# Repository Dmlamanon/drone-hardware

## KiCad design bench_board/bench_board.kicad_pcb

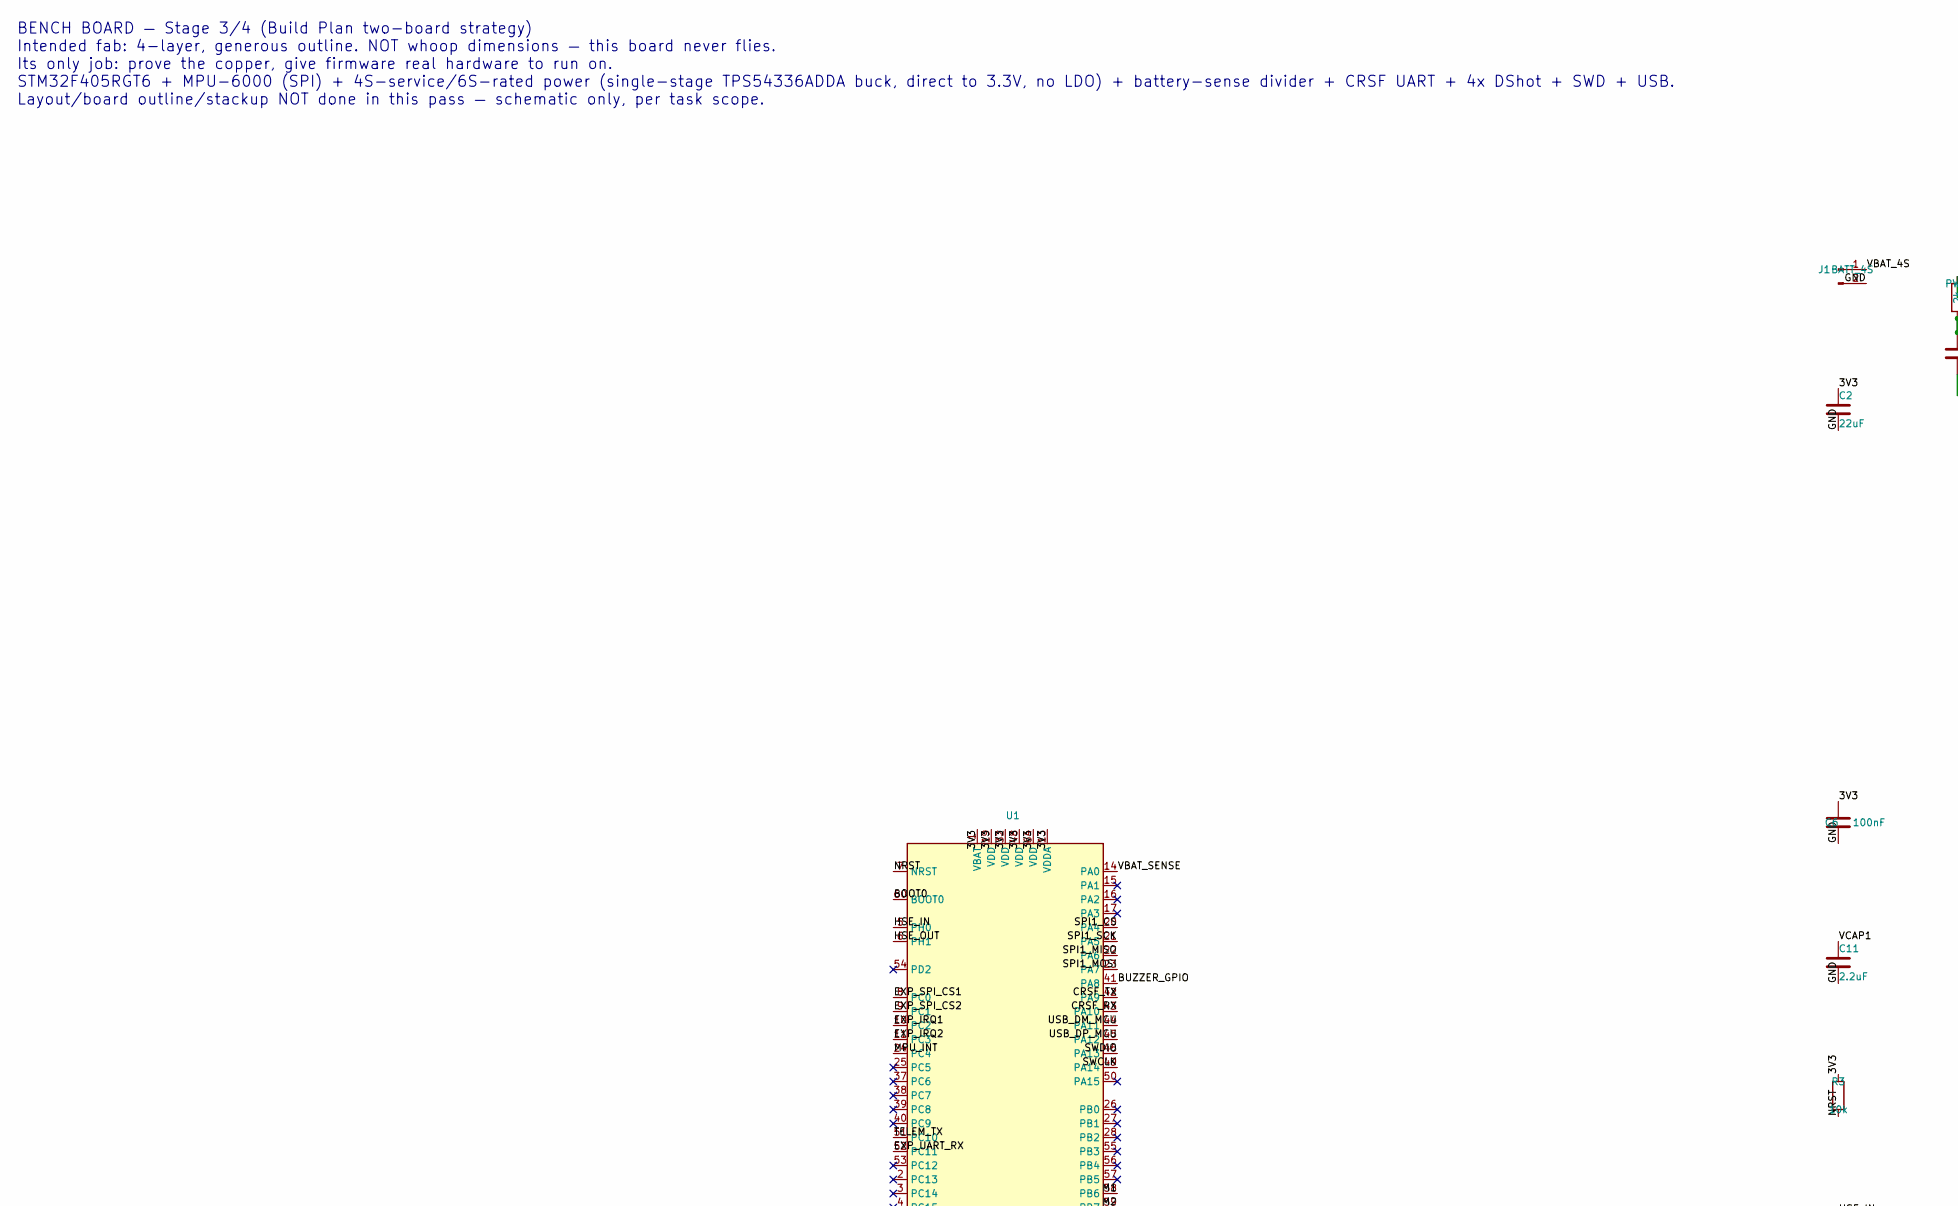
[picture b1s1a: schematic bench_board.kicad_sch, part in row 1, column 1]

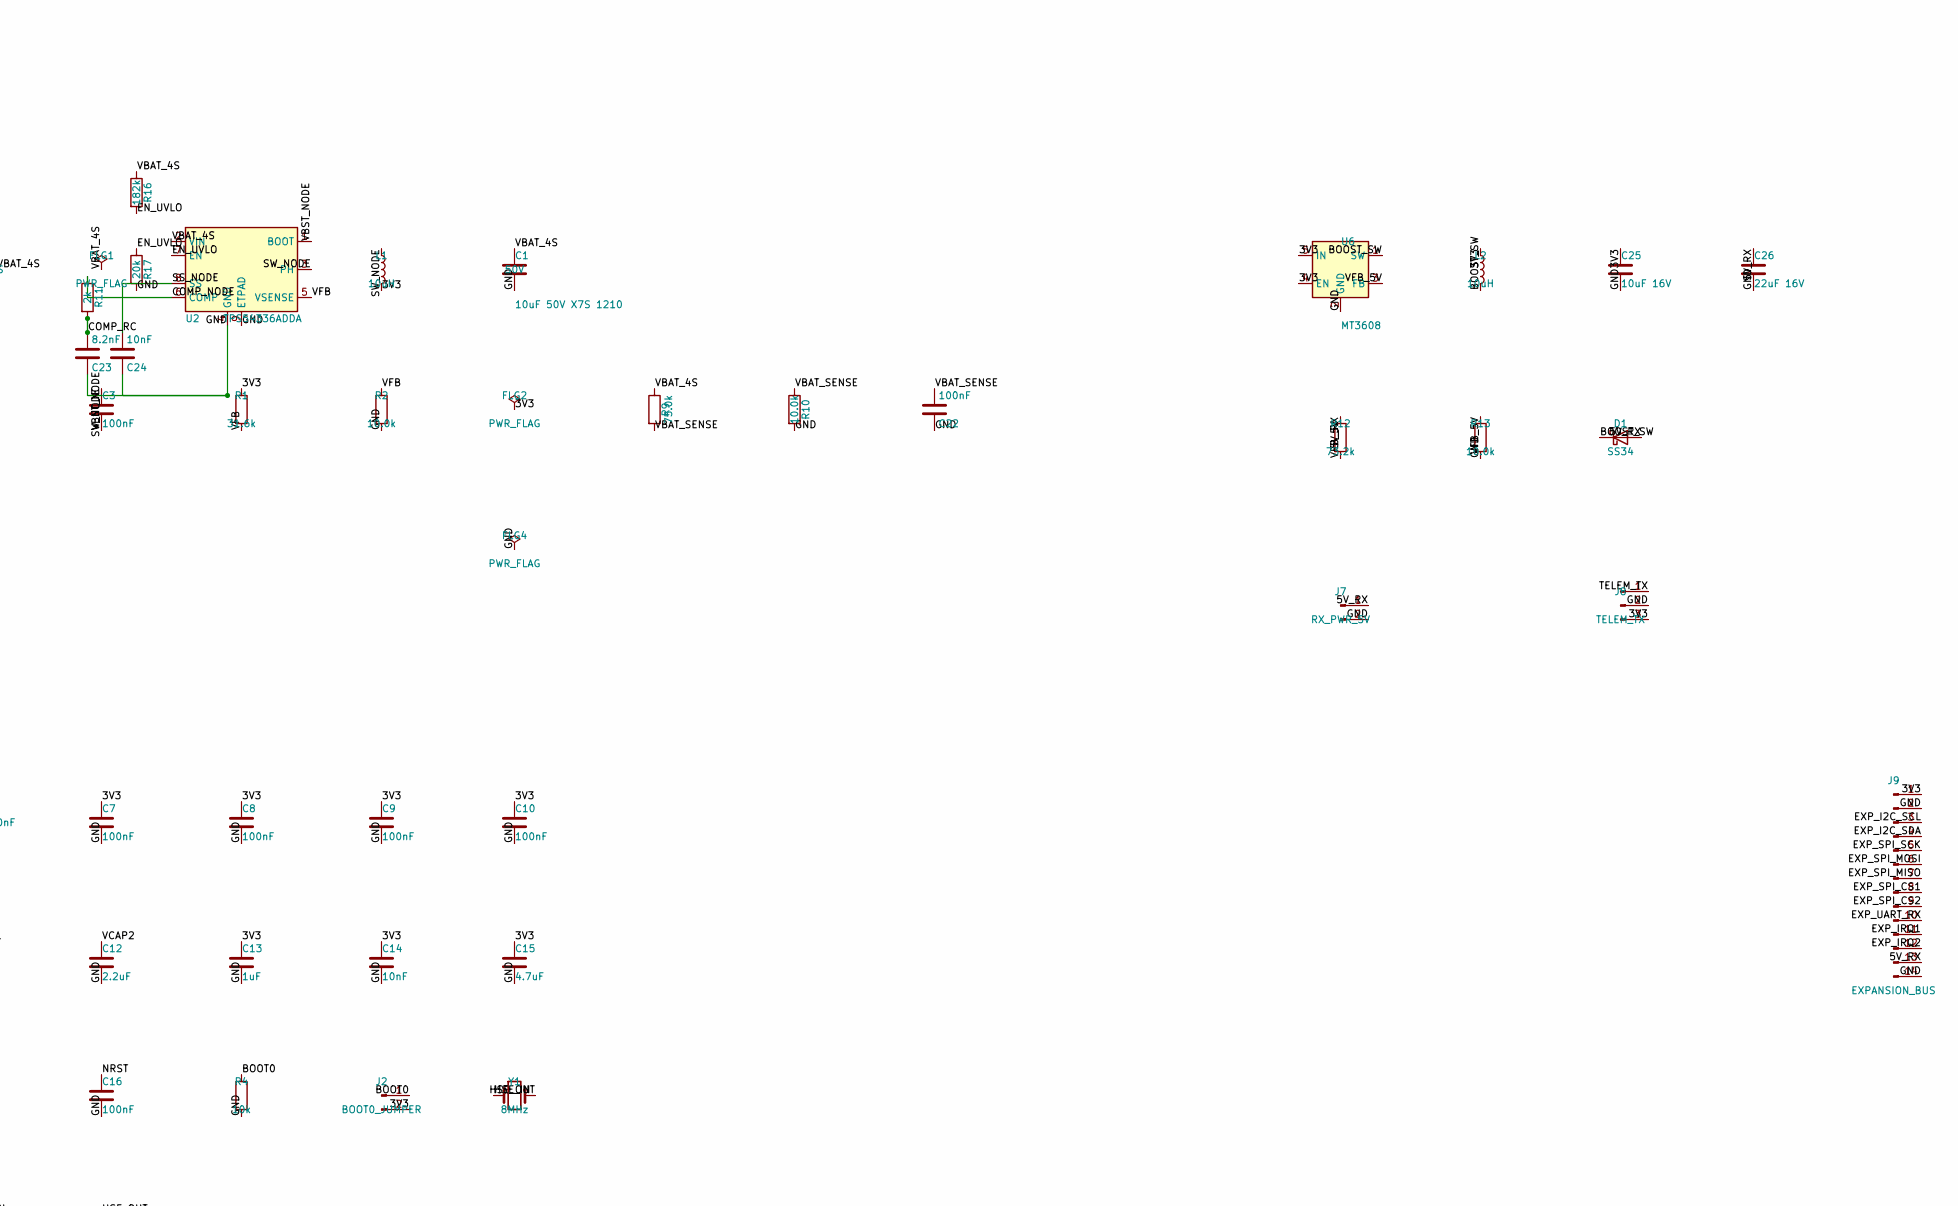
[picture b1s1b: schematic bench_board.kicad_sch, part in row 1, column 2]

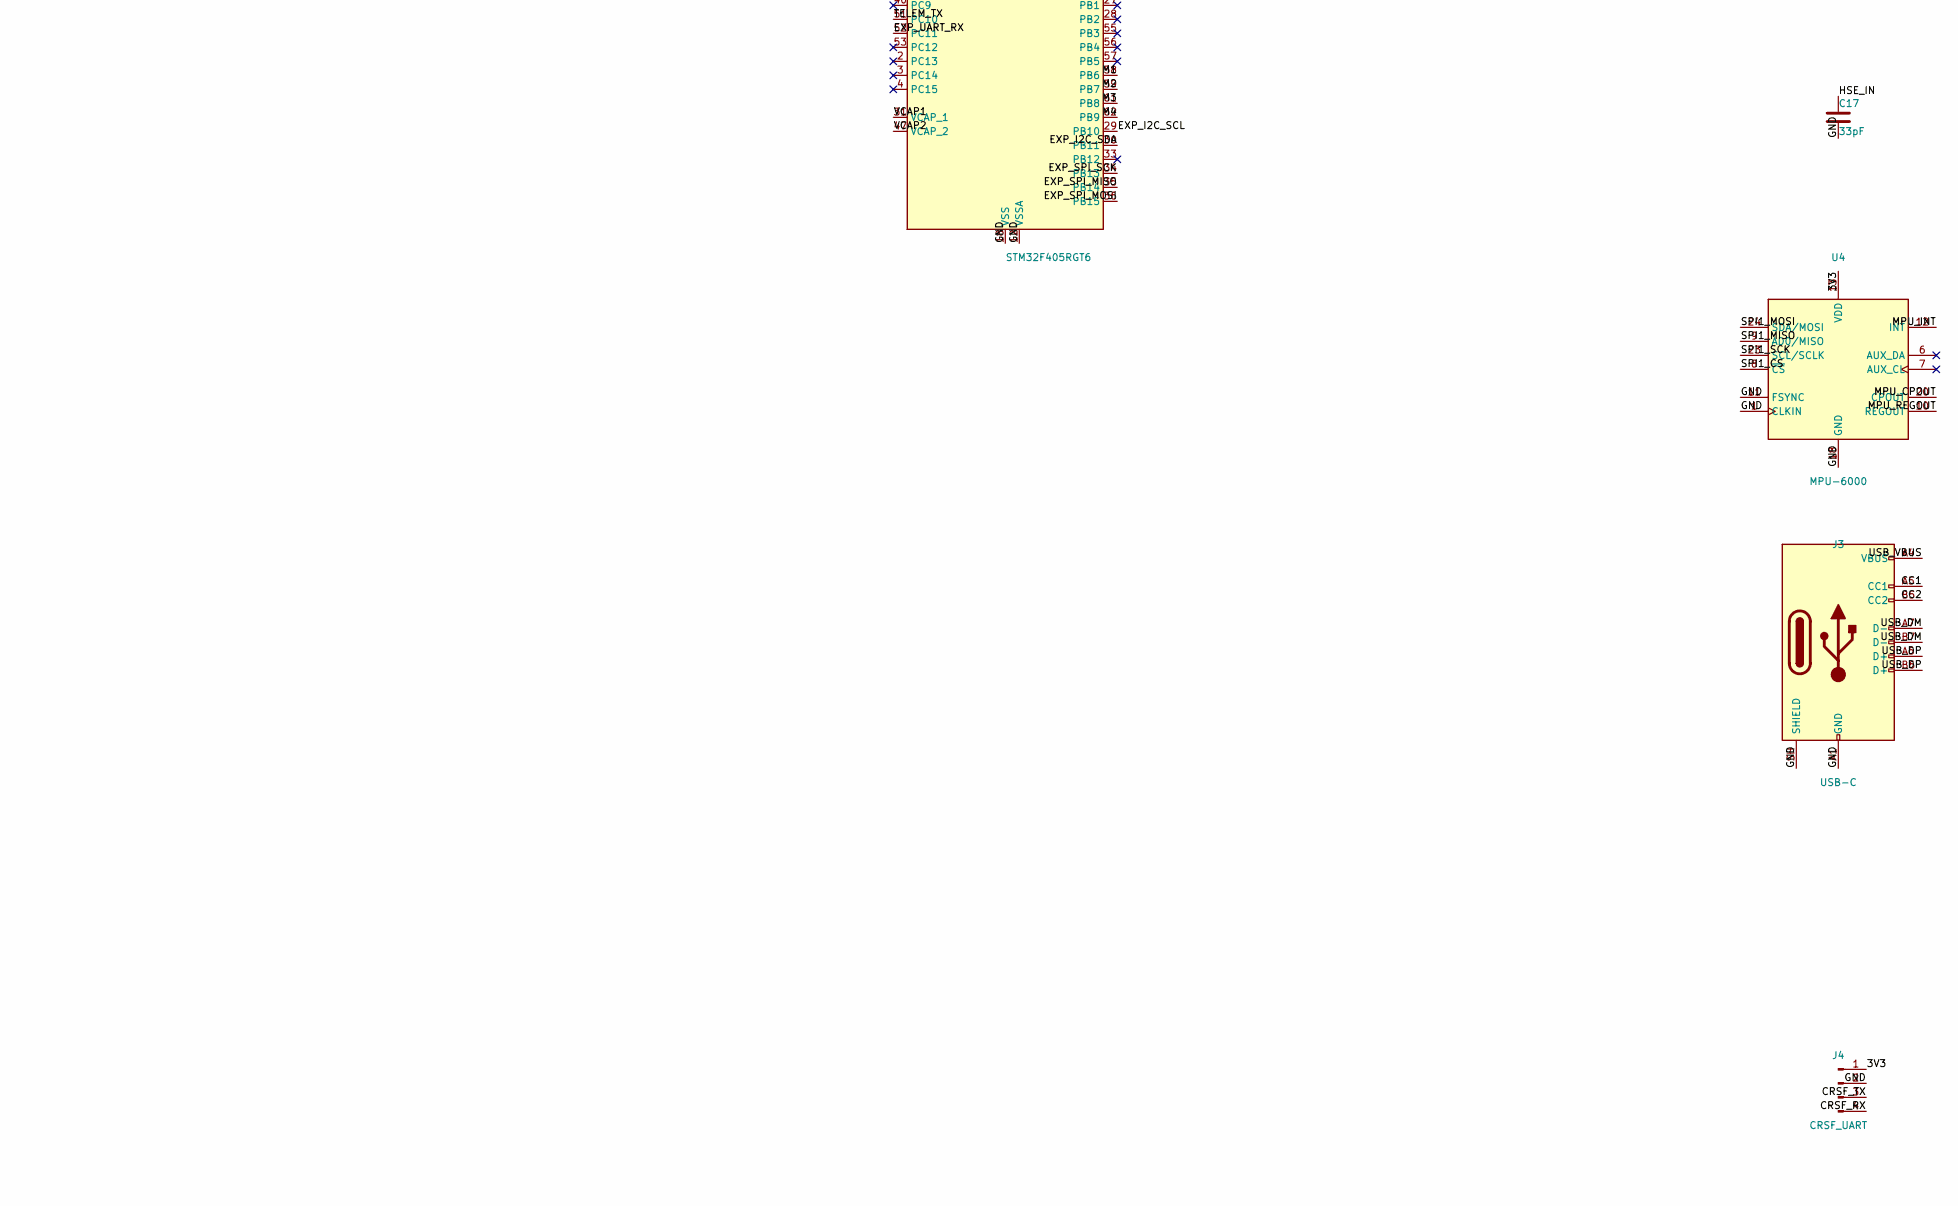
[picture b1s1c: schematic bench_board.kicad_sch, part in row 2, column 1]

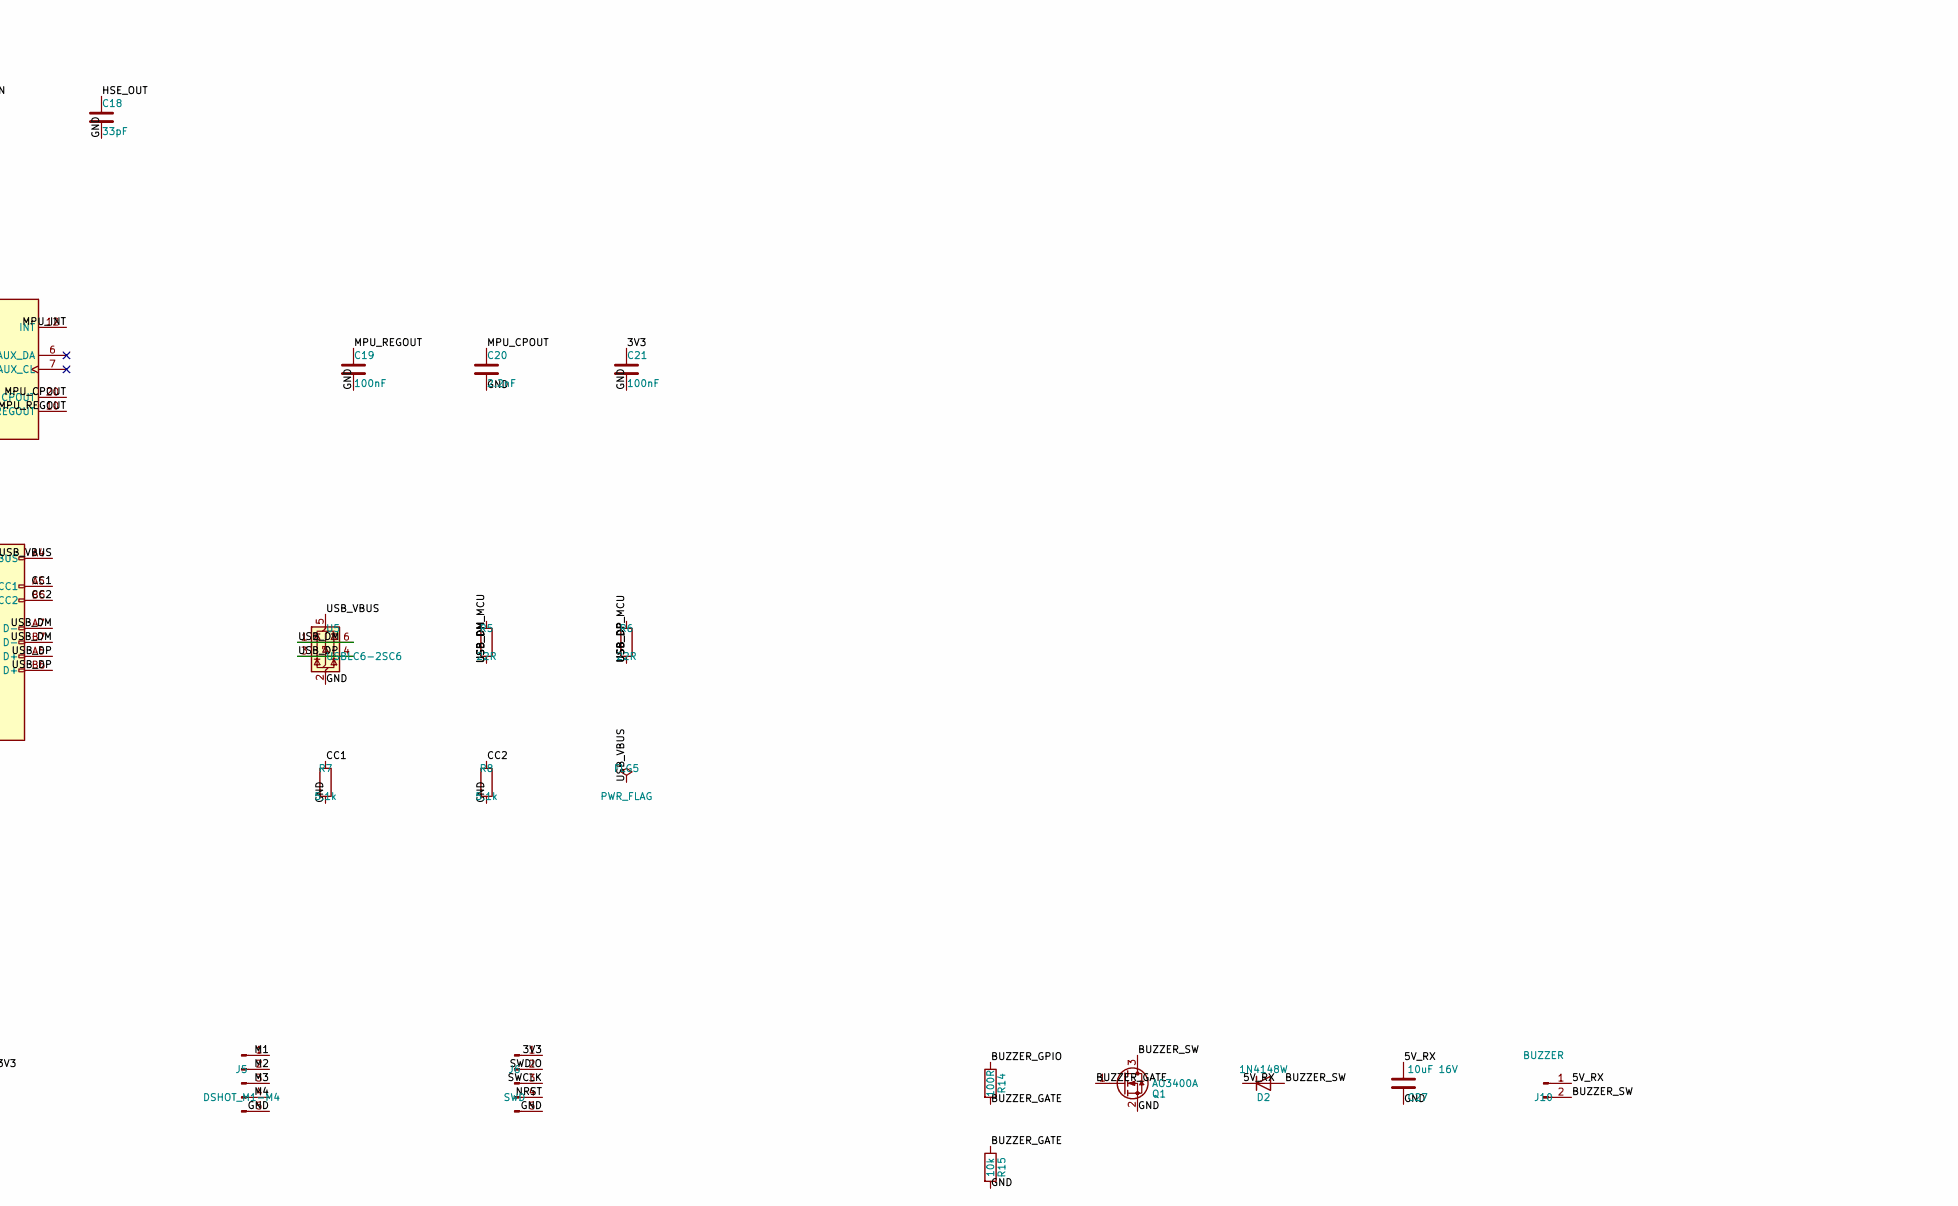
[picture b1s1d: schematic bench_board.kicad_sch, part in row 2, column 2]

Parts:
C1: 10uF 50V X7S 1210; C_1210_3225Metric; Voltage 50V; MPN GRM32ER71H106KA12L
C2: 22uF; C_0805_2012Metric
C3, C6, C7, C8, C9, C10, C16, C19, C21, C22: 100nF; C_0402_1005Metric
C11, C12: 2.2uF; C_0603_1608Metric
C13: 1uF; C_0603_1608Metric
C14, C24: 10nF; C_0402_1005Metric
C15: 4.7uF; C_0805_2012Metric
C17, C18: 33pF; C_0402_1005Metric; Voltage 50V; LCSC C1562
C20: 2.2nF; C_0402_1005Metric; Voltage 50V; LCSC C106861
C23: 8.2nF; C_0402_1005Metric
C25, C27: 10uF 16V; C_0805_2012Metric
C26: 22uF 16V; C_0805_2012Metric
D1: SS34; D_SMA
D2: 1N4148W; D_SOD-123
FLG1, FLG2, FLG4, FLG5: PWR_FLAG
J1: BATT_4S; PinHeader_1x02_P2.54mm_Vertical
J2: BOOT0_JUMPER; PinHeader_1x02_P2.54mm_Vertical
J3: USB-C; USB_C_Receptacle_Amphenol_12401548E4-2A
J4: CRSF_UART; PinHeader_1x04_P2.54mm_Vertical
J5: DSHOT_M1-M4; PinHeader_1x05_P2.54mm_Vertical
J6: SWD; PinHeader_1x05_P2.54mm_Vertical
J7: RX_PWR_5V; PinHeader_1x02_P2.54mm_Vertical
J8: TELEM_TX; PinHeader_1x03_P2.54mm_Vertical
J9: EXPANSION_BUS; PinHeader_1x14_P2.54mm_Vertical
J10: BUZZER; PinHeader_1x02_P2.54mm_Vertical
L1, L2: 10uH; L_1210_3225Metric
Q1: AO3400A; SOT-23
R1: 31.6k; R_0402_1005Metric
R2, R10: 10.0k; R_0402_1005Metric
R3, R4, R15: 10k; R_0402_1005Metric
R5, R6: 22R; R_0402_1005Metric
R7, R8: 5.1k; R_0402_1005Metric
R9: 75.0k; R_0402_1005Metric
R11: 2k; R_0402_1005Metric
R12: 73.2k; R_0603_1608Metric
R13: 10.0k; R_0603_1608Metric
R14: 100R; R_0402_1005Metric
R16: 182k; R_0402_1005Metric; Tolerance 1%; LCSC C11481
R17: 20k; R_0402_1005Metric; Tolerance 1%; LCSC C25765
U1: STM32F405RGT6; LQFP-64_10x10mm_P0.5mm
U2: TPS54336ADDA; SOIC-8-1EP_3.9x4.9mm_P1.27mm_EP2.41x3.81mm
U4: MPU-6000; InvenSense_QFN-24_4x4mm_P0.5mm
U5: USBLC6-2SC6; SOT-23-6
U6: MT3608; SOT-23-6
Y1: 8MHz; Crystal_SMD_5032-2Pin_5.0x3.2mm; LCSC C115962

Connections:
/3V3: C2.1, C6.1, C7.1, C8.1, C9.1, C10.1, C13.1, C14.1, C15.1, C21.1, C25.1, FLG2.1, J2.2, J4.1, J6.1, J8.3, J9.1, L1.2, L2.1, R1.1, R3.1, U1.1 (VBAT), U1.13 (VDDA), U1.19 (VDD), U1.32 (VDD), U1.48 (VDD), U1.64 (VDD), U4.13 (VDD), U6.4 (EN), U6.5 (IN)
/5V_RX: C26.1, C27.1, D1.2 (A), D2.1 (K), J7.1, J9.13, J10.1, R12.1
/BOOST_SW: D1.1 (K), L2.2, U6.1 (SW)
/BOOT0: J2.1, R4.1, U1.60 (BOOT0)
/BUZZER_GATE: Q1.1 (G), R14.2, R15.1
/BUZZER_GPIO: R14.1, U1.41 (PA8)
/BUZZER_SW: D2.2 (A), J10.2, Q1.3 (D)
/CC1: J3.A5 (CC1), R7.1
/CC2: J3.B5 (CC2), R8.1
/COMP_NODE: R11.1, U2.6 (COMP)
/COMP_RC: C23.1, R11.2
/CRSF_RX: J4.4, U1.43 (PA10)
/CRSF_TX: J4.3, U1.42 (PA9)
/EN_UVLO: R16.2, R17.1, U2.7 (EN)
/EXP_I2C_SCL: J9.3, U1.29 (PB10)
/EXP_I2C_SDA: J9.4, U1.30 (PB11)
/EXP_IRQ1: J9.11, U1.10 (PC2)
/EXP_IRQ2: J9.12, U1.11 (PC3)
/EXP_SPI_CS1: J9.8, U1.8 (PC0)
/EXP_SPI_CS2: J9.9, U1.9 (PC1)
/EXP_SPI_MISO: J9.7, U1.35 (PB14)
/EXP_SPI_MOSI: J9.6, U1.36 (PB15)
/EXP_SPI_SCK: J9.5, U1.34 (PB13)
/EXP_UART_RX: J9.10, U1.52 (PC11)
/GND: C1.2, C2.2, C6.2, C7.2, C8.2, C9.2, C10.2, C11.2, C12.2, C13.2, C14.2, C15.2, C16.2, C17.2, C18.2, C19.2, C20.2, C21.2, C22.2, C23.2, C24.2, C25.2, C26.2, C27.2, FLG4.1, J1.2, J3.A1 (GND), J3.A12 (GND), J3.B1 (GND), J3.B12 (GND), J3.SH (SHIELD), J4.2, J5.5, J6.5, J7.2, J8.2, J9.2, J9.14, Q1.2 (S), R2.2, R4.2, R7.2, R8.2, R10.2, R13.2, R15.2, R17.2, U1.12 (VSSA), U1.18 (VSS), U1.63 (VSS), U2.4 (GND), U2.9 (ETPAD), U4.1 (CLKIN), U4.11 (FSYNC), U4.18 (GND), U5.2 (GND), U6.2 (GND)
/HSE_IN: C17.1, U1.5 (PH0), Y1.1
/HSE_OUT: C18.1, U1.6 (PH1), Y1.2
/M1: J5.1, U1.58 (PB6)
/M2: J5.2, U1.59 (PB7)
/M3: J5.3, U1.61 (PB8)
/M4: J5.4, U1.62 (PB9)
/MPU_CPOUT: C20.1, U4.20 (CPOUT)
/MPU_INT: U1.24 (PC4), U4.12 (INT)
/MPU_REGOUT: C19.1, U4.10 (REGOUT)
/NRST: C16.1, J6.4, R3.2, U1.7 (NRST)
/SPI1_CS: U1.20 (PA4), U4.8 (~CS)
/SPI1_MISO: U1.22 (PA6), U4.9 (AD0/MISO)
/SPI1_MOSI: U1.23 (PA7), U4.24 (SDA/MOSI)
/SPI1_SCK: U1.21 (PA5), U4.23 (SCL/SCLK)
/SS_NODE: C24.1, U2.8 (SS)
/SWCLK: J6.3, U1.49 (PA14)
/SWDIO: J6.2, U1.46 (PA13)
/SW_NODE: C3.1, L1.1, U2.3 (PH)
/TELEM_TX: J8.1, U1.51 (PC10)
/USB_DM: J3.A7 (D-), J3.B7 (D-), R5.1, U5.1 (I/O1), U5.6 (I/O1)
/USB_DM_MCU: R5.2, U1.44 (PA11)
/USB_DP: J3.A6 (D+), J3.B6 (D+), R6.1, U5.3 (I/O2), U5.4 (I/O2)
/USB_DP_MCU: R6.2, U1.45 (PA12)
/USB_VBUS: FLG5.1, J3.A4 (VBUS), J3.A9 (VBUS), J3.B4 (VBUS), J3.B9 (VBUS), U5.5 (VBUS)
/VBAT_4S: C1.1, FLG1.1, J1.1, R9.1, R16.1, U2.2 (VIN)
/VBAT_SENSE: C22.1, R9.2, R10.1, U1.14 (PA0)
/VBST_NODE: C3.2, U2.1 (BOOT)
/VCAP1: C11.1, U1.31 (VCAP_1)
/VCAP2: C12.1, U1.47 (VCAP_2)
/VFB: R1.2, R2.1, U2.5 (VSENSE)
/VFB_5V: R12.2, R13.1, U6.3 (FB)

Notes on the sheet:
BENCH BOARD — Stage 3/4 (Build Plan two-board strategy) Intended fab: 4-layer, generous outline. NOT whoop dimensions — this board never flies. Its only job: prove the copper, give firmware real hardware to run on. STM32F405RGT6 + MPU-6000 (SPI) + 4S-service/6S-rated power (single-stage TPS54336ADD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

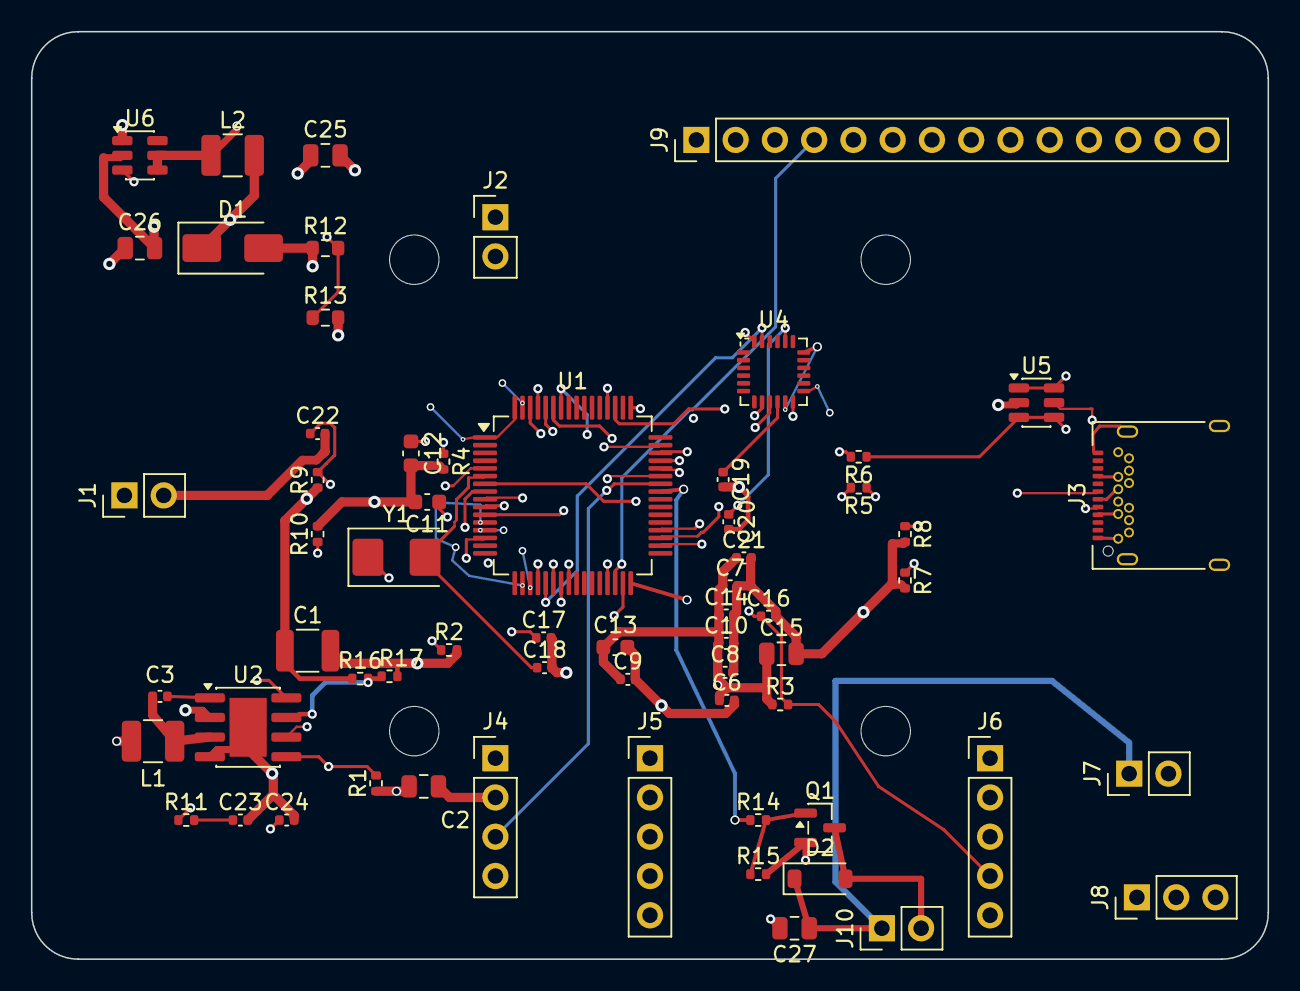
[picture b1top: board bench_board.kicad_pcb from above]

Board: 4 copper layers, 80.0 x 60.0 mm, 67 parts (0 on the bottom side), 56 nets.

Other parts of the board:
MH1, MH2, MH3, MH4: MountingHole_3.2mm; MountingHole_3.2mm_M3

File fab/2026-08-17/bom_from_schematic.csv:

"Reference","Value","Footprint","LCSC","JLCPCB_PN","QUANTITY"
"C1","10uF 50V X7R 1210","Capacitor_SMD:C_1210_3225Metric","","","1"
"C2","22uF","Capacitor_SMD:C_0805_2012Metric","","","1"
"C3,C6-C10,C16,C19-C22","100nF","Capacitor_SMD:C_0402_1005Metric","","","11"
"C11,C12","2.2uF","Capacitor_SMD:C_0603_1608Metric","","","2"
"C13","1uF","Capacitor_SMD:C_0603_1608Metric","","","1"
"C14,C24","10nF","Capacitor_SMD:C_0402_1005Metric","","","2"
"C15","4.7uF","Capacitor_SMD:C_0805_2012Metric","","","1"
"C17,C18","10pF","Capacitor_SMD:C_0402_1005Metric","","","2"
"C23","7.5nF","Capacitor_SMD:C_0402_1005Metric","","","1"
"C25","10uF 16V","Capacitor_SMD:C_0805_2012Metric","","","1"
"C26","22uF 16V","Capacitor_SMD:C_0805_2012Metric","","","1"
"D1","SS34","Diode_SMD:D_SMA","","","1"
"FLG1,FLG2,FLG4,FLG5","PWR_FLAG","","","","4"
"J1","BATT_4S","Connector_PinHeader_2.54mm:PinHeader_1x02_P2.54mm_Vertical","","","1"
"J2","BOOT0_JUMPER","Connector_PinHeader_2.54mm:PinHeader_1x02_P2.54mm_Vertical","","","1"
"J3","USB-C","Connector_USB:USB_C_Receptacle_Amphenol_12401548E4-2A","","","1"
"J4","CRSF_UART","Connector_PinHeader_2.54mm:PinHeader_1x04_P2.54mm_Vertical","","","1"
"J5","DSHOT_M1-M4","Connector_PinHeader_2.54mm:PinHeader_1x05_P2.54mm_Vertical","","","1"
"J6","SWD","Connector_PinHeader_2.54mm:PinHeader_1x05_P2.54mm_Vertical","","","1"
"J7","RX_PWR_5V","Connector_PinHeader_2.54mm:PinHeader_1x02_P2.54mm_Vertical","","","1"
"J8","TELEM_TX","Connector_PinHeader_2.54mm:PinHeader_1x03_P2.54mm_Vertical","","","1"
"J9","EXPANSION_BUS","Connector_PinHeader_2.54mm:PinHeader_1x14_P2.54mm_Vertical","","","1"
"L1,L2","10uH","Inductor_SMD:L_1210_3225Metric","","","2"
"R1","31.6k","Resistor_SMD:R_0402_1005Metric","","","1"
"R2,R10","10.0k","Resistor_SMD:R_0402_1005Metric","","","2"
"R3,R4","10k","Resistor_SMD:R_0402_1005Metric","","","2"
"R5,R6","22R","Resistor_SMD:R_0402_1005Metric","","","2"
"R7,R8","5.1k","Resistor_SMD:R_0402_1005Metric","","","2"
"R9","75.0k","Resistor_SMD:R_0402_1005Metric","","","1"
"R11","2k","Resistor_SMD:R_0402_1005Metric","","","1"
"R12","73.2k","Resistor_SMD:R_0603_1608Metric","","","1"
"R13","10.0k","Resistor_SMD:R_0603_1608Metric","","","1"
"U1","STM32F405RGT6","Package_QFP:LQFP-64_10x10mm_P0.5mm","","","1"
"U2","TPS54336ADDA","Package_SO:SOIC-8-1EP_3.9x4.9mm_P1.27mm_EP2.41x3.81mm","","","1"
"U4","MPU-6000","Sensor_Motion:InvenSense_QFN-24_4x4mm_P0.5mm","","","1"
"U5","USBLC6-2SC6","Package_TO_SOT_SMD:SOT-23-6","","","1"
"U6","MT3608","Package_TO_SOT_SMD:SOT-23-6","","","1"
"Y1","8MHz","Crystal:Crystal_SMD_5032-2Pin_5.0x3.2mm","C115962","C115962","1"
